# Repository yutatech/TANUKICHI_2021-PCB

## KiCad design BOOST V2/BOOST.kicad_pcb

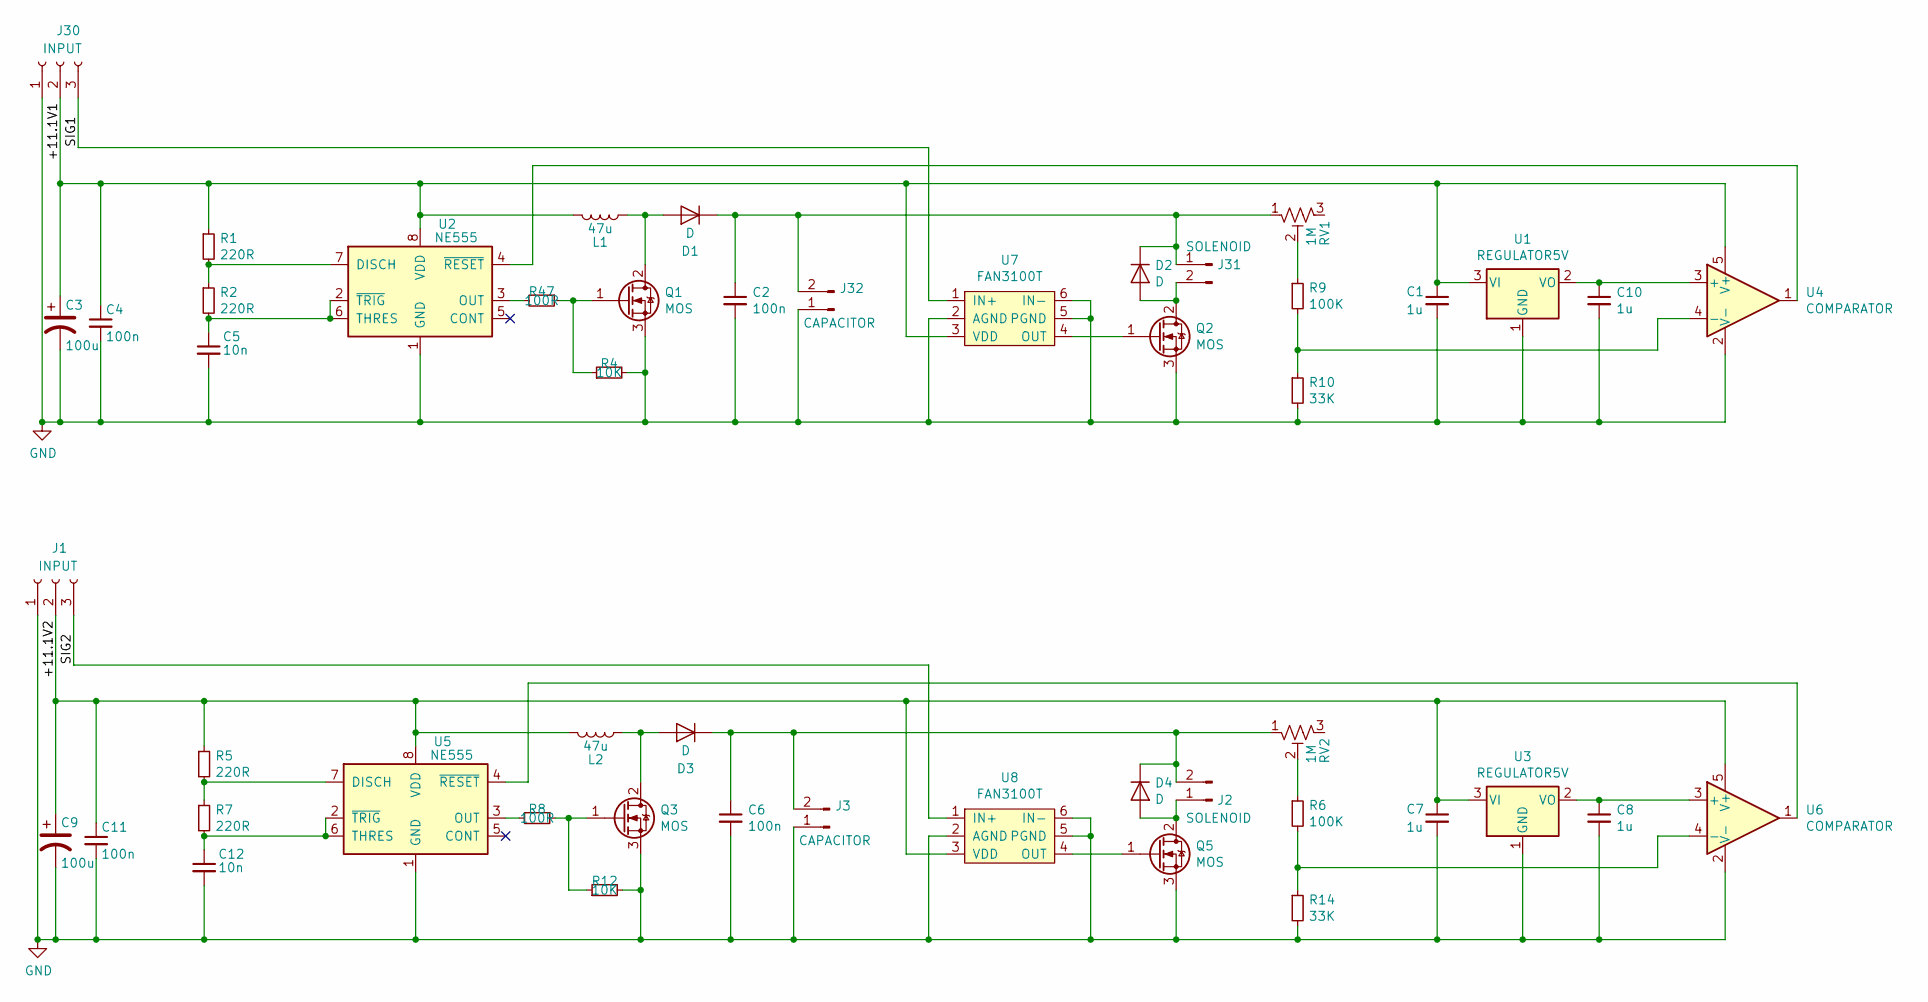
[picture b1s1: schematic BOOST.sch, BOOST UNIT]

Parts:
C1, C7, C8, C10: 1u; 1608
C2, C4, C6, C11: 100n; 1005
C3, C9: 100u; TANTALCAP-6032; Part # F931C107MCCAJ6
C5, C12: 10n; 1005
D1, D2, D3, D4: D; DO-214AC; Part # CDBA5200-HF
J1, J30: INPUT; 3Pads
J2, J31: SOLENOID; Molex_2pin_angled
J3, J32: CAPACITOR; 2Pads
L1, L2: 47u; Inductor_10x10x3.8
Q1, Q3: MOS; TO-252; Part # SUD80460E-GE3
Q2, Q5: MOS; TO-252; Part # IXFY36N20X3
R1, R2, R5, R7: 220R; 1005
R4, R12: 10K; 1005
R6, R9: 100K; 1005
R8, R47: 100R; 1005
R10, R14: 33K; 1005
RV1: 1M; CONN_01x03; Part @ 3296W-1-103
RV2: 1M; CONN_01x03; Part # 3296W-1-103
U1, U3: REGULATOR5V; SOT-23; Part # MCP1799T-5002H/TT
U2, U5: NE555; SOIC-8
U4, U6: COMPARATOR; SOT-23-5; Part # MIC6270YM5-TR
U7, U8: FAN3100T; VDFN-6; Part # FAN3100TMPX

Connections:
/+11.1V1: C1.1, C3.1, C4.1, J30.2, L1.2, R1.1, U1.3 (VI), U2.8 (VDD), U4.5 (V+), U7.3 (VDD)
/+11.1V2: C7.1, C9.1, C11.1, J1.2, L2.2, R5.1, U3.3 (VI), U5.8 (VDD), U6.5 (V+), U8.3 (VDD)
/SIG1: J30.3, U7.1 (IN+)
/SIG2: J1.3, U8.1 (IN+)
GND: C1.2, C2.2, C3.2, C4.2, C5.2, C6.2, C7.2, C8.2, C9.2, C10.2, C11.2, C12.2, J1.1, J3.1, J30.1, J32.1, Q1.3 (S), Q2.3 (S), Q3.3 (S), Q5.3 (S), R4.2, R10.2, R12.2, R14.2, U1.1 (GND), U2.1 (GND), U3.1 (GND), U4.2 (V-), U5.1 (GND), U6.2 (V-), U7.2 (AGND), U7.5 (PGND), U7.6 (IN-), U8.2 (AGND), U8.5 (PGND), U8.6 (IN-)
unnamed: C2.1, D1.1 (K), D2.1 (K), J31.1, J32.2, RV1.1
unnamed: C5.1, R2.2, U2.2 (~TRIG), U2.6 (THRES)
unnamed: C6.1, D3.1 (K), D4.1 (K), J2.2, J3.2, RV2.1
unnamed: C8.1, U3.2 (VO), U6.3 (+)
unnamed: C10.1, U1.2 (VO), U4.3 (+)
unnamed: C12.1, R7.2, U5.2 (~TRIG), U5.6 (THRES)
unnamed: D1.2 (A), L1.1, Q1.2 (D)
unnamed: D2.2 (A), J31.2, Q2.2 (D)
unnamed: D3.2 (A), L2.1, Q3.2 (D)
unnamed: D4.2 (A), J2.1, Q5.2 (D)
unnamed: Q1.1 (G), R4.1, R47.1
unnamed: Q2.1 (G), U7.4 (OUT)
unnamed: Q3.1 (G), R8.1, R12.1
unnamed: Q5.1 (G), U8.4 (OUT)
unnamed: R1.2, R2.1, U2.7 (DISCH)
unnamed: R5.2, R7.1, U5.7 (DISCH)
unnamed: R6.1, RV2.2
unnamed: R8.2, U5.3 (OUT)
unnamed: R9.1, RV1.2
unnamed: R9.2, R10.1, U4.4 (-)
unnamed: R6.2, R14.1, U6.4 (-)
unnamed: R47.2, U2.3 (OUT)
unnamed: U2.4 (~RESET), U4.1
unnamed: U5.4 (~RESET), U6.1

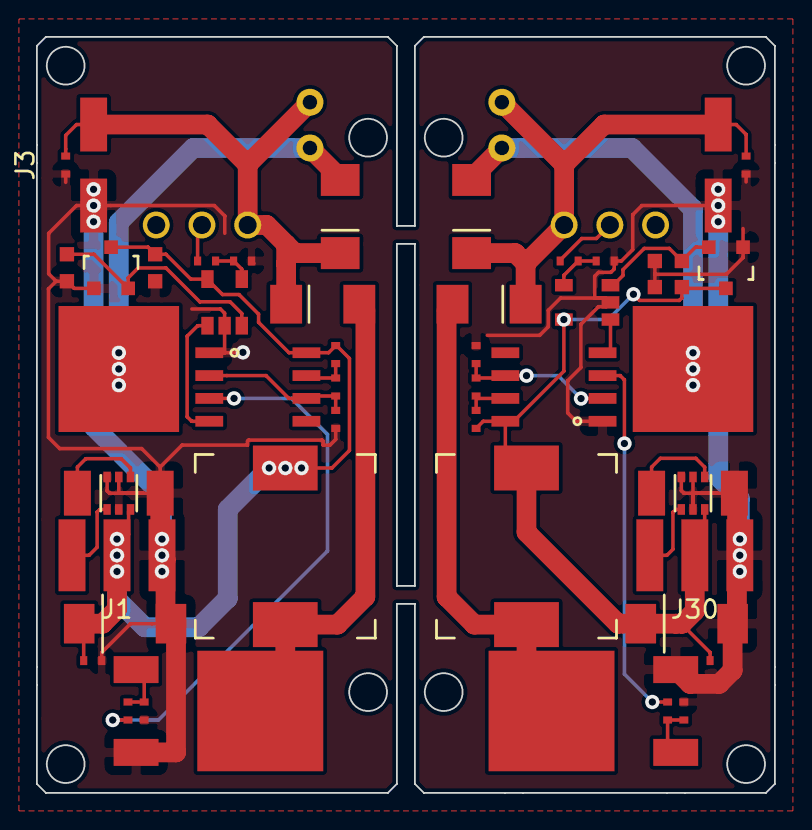
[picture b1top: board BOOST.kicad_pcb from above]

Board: 2 copper layers, 41.0 x 42.0 mm, 50 parts (0 on the bottom side), 29 nets.
